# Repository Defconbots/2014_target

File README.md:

# Defconbots 2014 Target Hardware/Firmware

## Overview

This is the hardware and firmware design files for the defconbots 2014 laser target. It uses an [MSP430G2452](http://www.ti.com/product/msp430g2452) microcontroller and [TCS3414CS](http://www.ams.com/eng/Products/Light-Sensors/Color-Sensor/TCS3414) light detector to detect laser hits.

The board is designed in EagleCad 6.x. All part numbers are mouser numbers for easy BOM export.

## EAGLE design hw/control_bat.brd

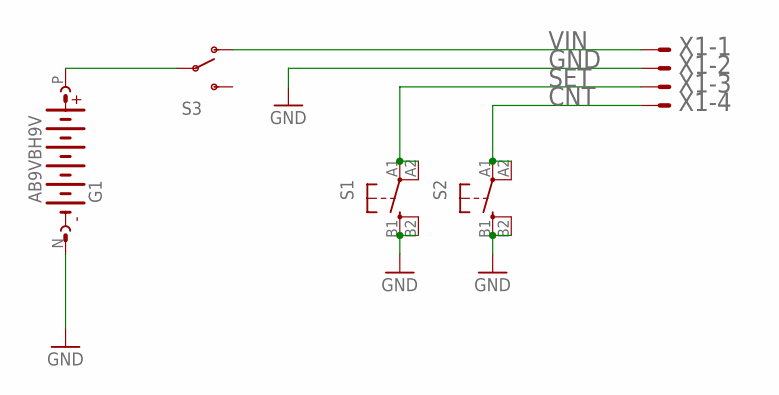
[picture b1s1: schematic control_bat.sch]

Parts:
G1: AB9VBH9V; BH9V-PC-ND
S1, S2: TAC_SWITCHD6F; D6F
S3: SWITCH-SPST; EG1270
X1: DF13-4P-1.25V(50); 53398-04

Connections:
CNT: S2.A1 (1), S2.A2 (2), X1.4
GND: G1.N (-), S1.B1 (3), S1.B2 (4), S2.B1 (3), S2.B2 (4), X1.2
unnamed: G1.P (+), S3.P$2
SET: S1.A1 (1), S1.A2 (2), X1.3
VIN: S3.P$1 (O), X1.1

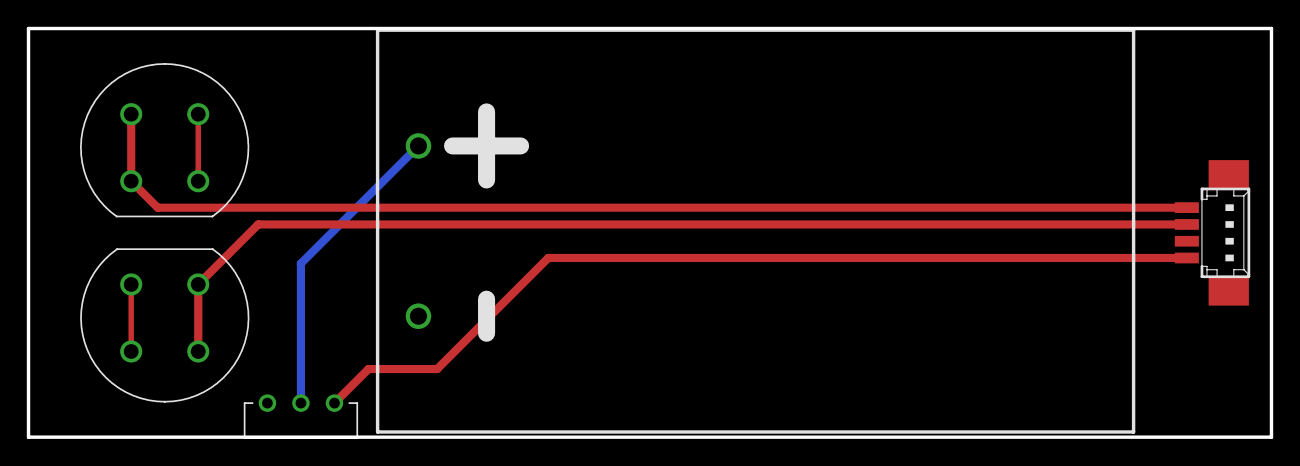
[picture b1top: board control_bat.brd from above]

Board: 2 copper layers, 92.7 x 30.5 mm, 5 parts (0 on the bottom side), 5 nets.

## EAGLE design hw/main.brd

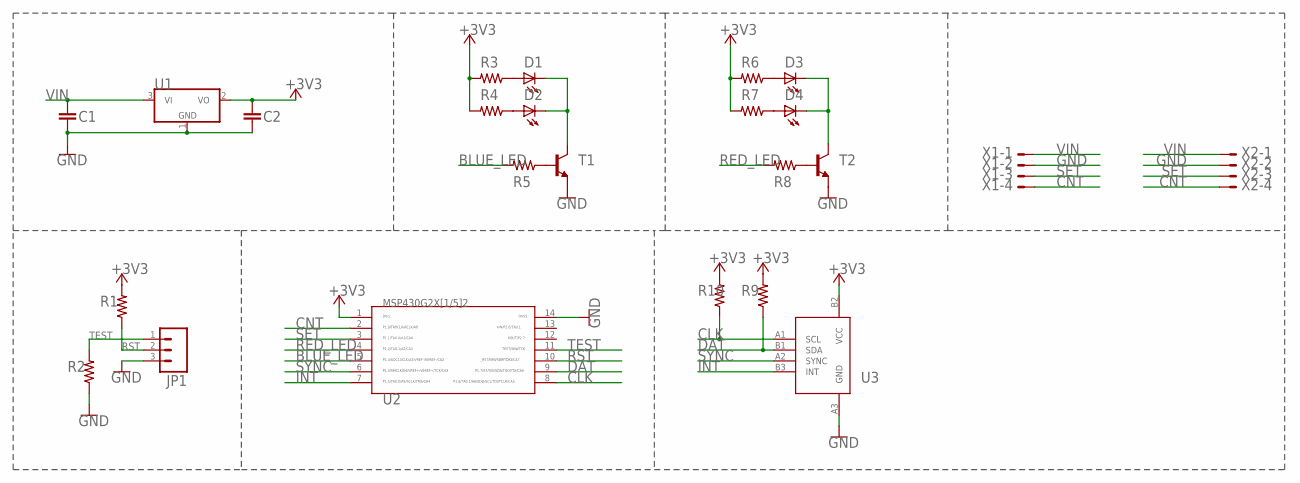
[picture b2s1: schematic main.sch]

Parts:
C1, C2: C1608X5R1C106M080AB; 0603-CAP
D1, D2: VLMB1300-GS08; LED-0603
D3, D4: VLMS1300-GS08; LED-0603
JP1: M03PTH; 1X03
R1, R2: RK73H1JTTD4702F; R0603
R3, R4, R5, R6, R7, R8: CRCW0603200RFKEA; R0603
R9, R10: RK73H1JTTD4701F; R0603
T1, T2: PMBT4401,215; SOT23-BEC
U1: MCP1703T-3002E/CB; SOT23
U2: MSP430G2452IPW14R; PW14
U3: TCS3414CS; CS-6
X1, X2: DF13-4P-1.25V(50); 53398-04

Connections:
+3V3: C2.1, R1.2, R3.2, R4.2, R6.2, R7.2, R9.2, R10.2, U1.2 (VO), U2.1, U3.B2 (VCC)
BLUE_LED: R5.2, U2.5
CLK: R10.1, U2.8, U3.A1 (SCL)
CNT: U2.2, X1.4, X2.4
DAT: R9.1, U2.9, U3.B1 (SDA)
GND: C1.2, C2.2, JP1.3, R2.1, T1.E, T2.E, U1.1 (GND), U2.14, U3.A3 (GND), X1.2, X2.2
INT: U2.7, U3.B3 (INT)
LED: D1.C, D2.C, T1.C
unnamed: D4.A, R7.1
unnamed: D3.C, D4.C, T2.C
unnamed: R8.1, T2.B
unnamed: D2.A, R4.1
unnamed: D1.A, R3.1
unnamed: D3.A, R6.1
unnamed: R5.1, T1.B
RED_LED: R8.2, U2.4
RST: JP1.2, R1.1, U2.10
SET: U2.3, X1.3, X2.3
SYNC: U2.6, U3.A2 (SYNC)
TEST: JP1.1, R2.2, U2.11
VIN: C1.1, U1.3 (VI), X1.1, X2.1

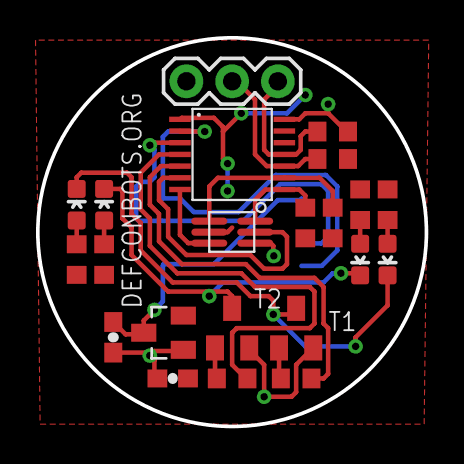
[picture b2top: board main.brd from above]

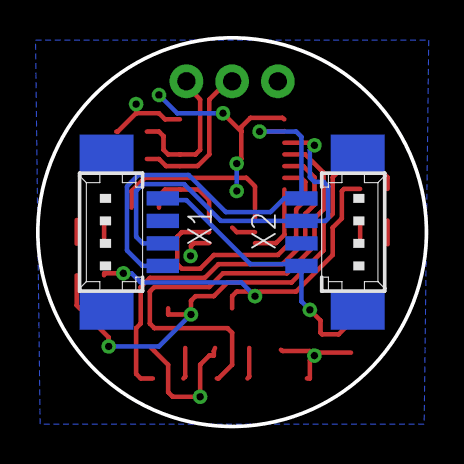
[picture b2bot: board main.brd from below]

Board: 2 copper layers, 21.6 x 21.6 mm, 24 parts (2 on the bottom side), 21 nets.

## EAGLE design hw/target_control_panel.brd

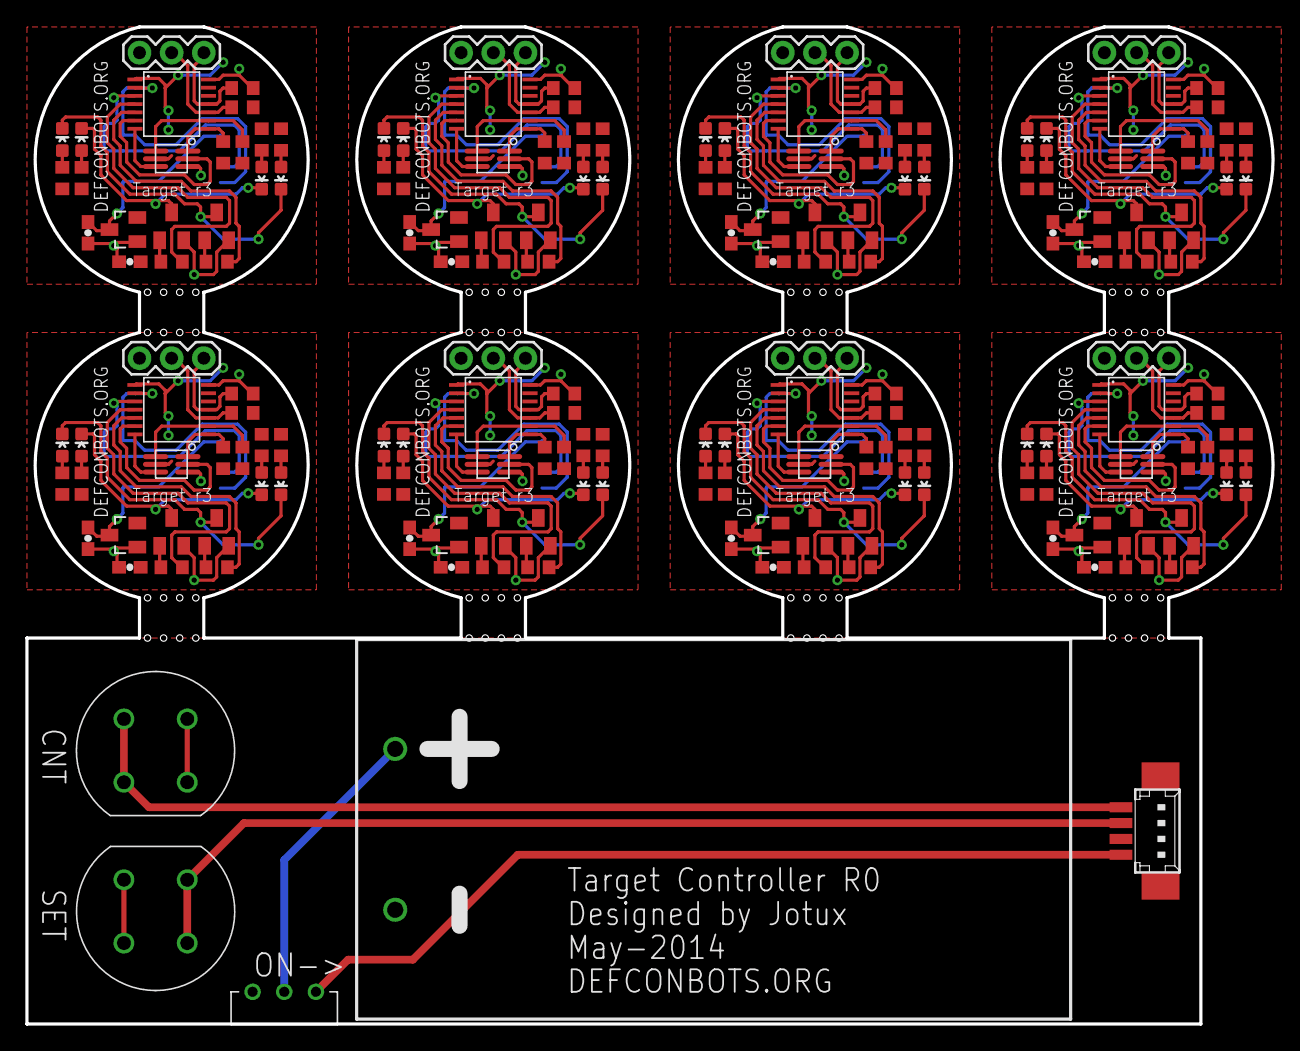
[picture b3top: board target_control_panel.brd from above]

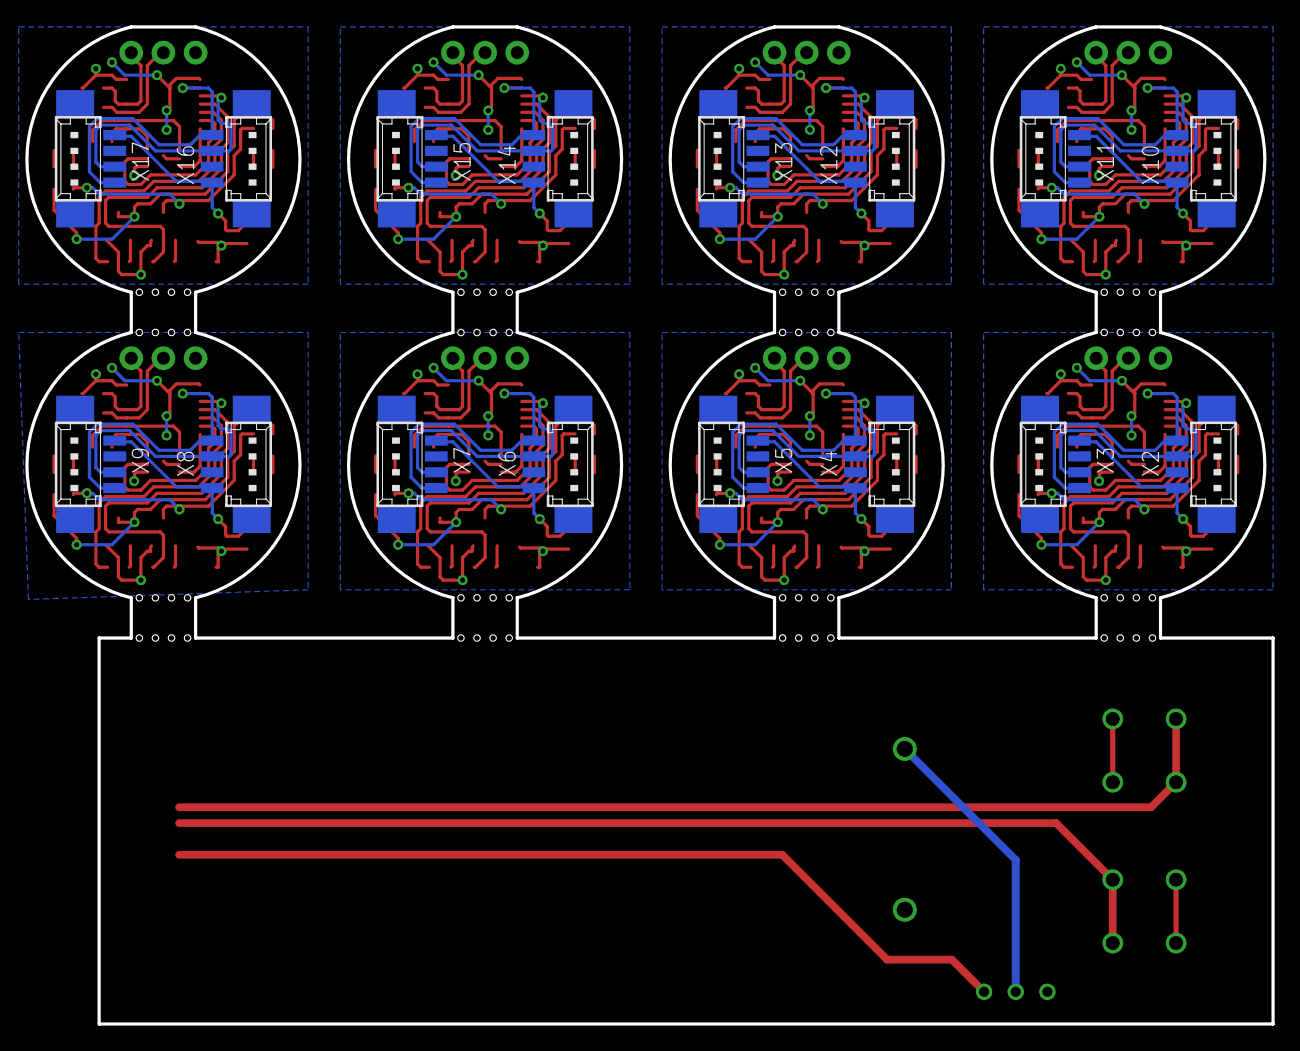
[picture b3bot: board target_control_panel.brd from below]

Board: 2 copper layers, 98.4 x 78.7 mm, 197 parts (16 on the bottom side), 173 nets.

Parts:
C1, C2, C3, C4, C5, C6, C7, C8, C9, C10, C11, C12, C13, C14, C15, C16: C1608X5R1C106M080AB; 0603-CAP
D1, D2, D5, D6, D9, D10, D13, D14, D17, D18, D21, D22, D25, D26, D29, D30: VLMB1300-GS08; LED-0603
D3, D4, D7, D8, D11, D12, D15, D16, D19, D20, D23, D24, D27, D28, D31, D32: VLMS1300-GS08; LED-0603
G1: AB9VBH9V; BH9V-PC-ND
JP1, JP2, JP3, JP4, JP5, JP6, JP7, JP8: 1X03
R1, R2, R15, R16, R25, R26, R35, R36, R45, R46, R55, R56, R65, R66, R75, R76: RK73H1JTTD4702F; R0603
R3, R4, R5, R6, R7, R8, R11, R12, R13, R14, R17, R18, R21, R22, R23, R24, R27, R28, R31, R32, R33, R34, R37, R38, R41, R42, R43, R44, R47, R48, R51, R52, R53, R54, R57, R58, R61, R62, R63, R64, R67, R68, R71, R72, R73, R74, R77, R78: CRCW0603200RFKEA; R0603
R9, R10, R19, R20, R29, R30, R39, R40, R49, R50, R59, R60, R69, R70, R79, R80: RK73H1JTTD4701F; R0603
S1, S2: D6F
S3: EG1270
T1, T2, T3, T4, T5, T6, T7, T8, T9, T10, T11, T12, T13, T14, T15, T16: PMBT4401,215; SOT23-BEC
U1, U4, U7, U10, U13, U16, U19, U22: MCP1703T-3002E/CB; SOT23
U2, U6, U9, U12, U15, U18, U21, U24: MSP430G2452IPW14R; PW14
U3, U5, U8, U11, U14, U17, U20, U23: TCS3414CS; CS-6
X1, X2, X3, X4, X5, X6, X7, X8, X9, X10, X11, X12, X13, X14, X15, X16, X17: DF13-4P-1.25V(50); 53398-04

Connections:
+3V1: C4.1, R11.2, R12.2, R14.2, R15.2, R17.2, R19.2, R20.2, U4.2, U5.B2, U6.1
+3V2: C6.1, R21.2, R22.2, R24.2, R25.2, R27.2, R29.2, R30.2, U7.2, U8.B2, U9.1
+3V3: C2.1, R1.2, R3.2, R4.2, R6.2, R7.2, R9.2, R10.2, U1.2, U2.1, U3.B2
+3V4: C8.1, R31.2, R32.2, R34.2, R35.2, R37.2, R39.2, R40.2, U10.2, U11.B2, U12.1
+3V5: C10.1, R41.2, R42.2, R44.2, R45.2, R47.2, R49.2, R50.2, U13.2, U14.B2, U15.1
+3V6: C12.1, R51.2, R52.2, R54.2, R55.2, R57.2, R59.2, R60.2, U16.2, U17.B2, U18.1
+3V7: C14.1, R61.2, R62.2, R64.2, R65.2, R67.2, R69.2, R70.2, U19.2, U20.B2, U21.1
+3V8: C16.1, R71.2, R72.2, R74.2, R75.2, R77.2, R79.2, R80.2, U22.2, U23.B2, U24.1
BLUE_LED: R5.2, U2.5
BLUE_LED1: R13.2, U6.5
BLUE_LED2: R23.2, U9.5
BLUE_LED3: R33.2, U12.5
BLUE_LED4: R43.2, U15.5
BLUE_LED5: R53.2, U18.5
BLUE_LED6: R63.2, U21.5
BLUE_LED7: R73.2, U24.5
CLK: R10.1, U2.8, U3.A1
CLK1: R20.1, U5.A1, U6.8
CLK2: R30.1, U8.A1, U9.8
CLK3: R40.1, U11.A1, U12.8
CLK4: R50.1, U14.A1, U15.8
CLK5: R60.1, U17.A1, U18.8
CLK6: R70.1, U20.A1, U21.8
CLK7: R80.1, U23.A1, U24.8
CNT: S2.A1, S2.A2, X1.4
CNT1: U2.2, X2.4, X3.4
CNT2: U6.2, X4.4, X5.4
CNT3: U9.2, X6.4, X7.4
CNT4: U12.2, X8.4, X9.4
CNT5: U15.2, X10.4, X11.4
CNT6: U18.2, X12.4, X13.4
CNT7: U21.2, X14.4, X15.4
CNT8: U24.2, X16.4, X17.4
DAT: R9.1, U2.9, U3.B1
DAT1: R19.1, U5.B1, U6.9
DAT2: R29.1, U8.B1, U9.9
DAT3: R39.1, U11.B1, U12.9
DAT4: R49.1, U14.B1, U15.9
DAT5: R59.1, U17.B1, U18.9
DAT6: R69.1, U20.B1, U21.9
DAT7: R79.1, U23.B1, U24.9
GND1: C1.2, C2.2, JP1.3, R2.1, T1.E, T2.E, U1.1, U2.14, U3.A3, X2.2, X3.2
GND2: C3.2, C4.2, JP2.3, R16.1, T3.E, T4.E, U4.1, U5.A3, U6.14, X4.2, X5.2
GND3: C5.2, C6.2, JP3.3, R26.1, T5.E, T6.E, U7.1, U8.A3, U9.14, X6.2, X7.2
GND4: C7.2, C8.2, JP4.3, R36.1, T7.E, T8.E, U10.1, U11.A3, U12.14, X8.2, X9.2
GND5: C9.2, C10.2, JP5.3, R46.1, T9.E, T10.E, U13.1, U14.A3, U15.14, X10.2, X11.2
GND6: C11.2, C12.2, JP6.3, R56.1, T11.E, T12.E, U16.1, U17.A3, U18.14, X12.2, X13.2
GND7: C13.2, C14.2, JP7.3, R66.1, T13.E, T14.E, U19.1, U20.A3, U21.14, X14.2, X15.2
GND8: C15.2, C16.2, JP8.3, R76.1, T15.E, T16.E, U22.1, U23.A3, U24.14, X16.2, X17.2
GND9: G1.N, S1.B1, S1.B2, S2.B1, S2.B2, X1.2
INT: U2.7, U3.B3
INT1: U5.B3, U6.7
INT2: U8.B3, U9.7
INT3: U11.B3, U12.7
INT4: U14.B3, U15.7
INT5: U17.B3, U18.7
INT6: U20.B3, U21.7
INT7: U23.B3, U24.7
LED: D1.C, D2.C, T1.C
LED1: D5.C, D6.C, T3.C
LED2: D9.C, D10.C, T5.C
LED3: D13.C, D14.C, T7.C
LED4: D17.C, D18.C, T9.C
LED5: D21.C, D22.C, T11.C
LED6: D25.C, D26.C, T13.C
LED7: D29.C, D30.C, T15.C
unnamed: D4.A, R7.1
unnamed: D3.C, D4.C, T2.C
unnamed: R8.1, T2.B
unnamed: G1.P, S3.P$2
unnamed: D5.A, R11.1
unnamed: D2.A, R4.1
unnamed: D1.A, R3.1
unnamed: D6.A, R12.1
unnamed: R13.1, T3.B
unnamed: D3.A, R6.1
unnamed: D7.A, R14.1
unnamed: D8.A, R17.1
unnamed: D7.C, D8.C, T4.C
unnamed: R18.1, T4.B
unnamed: D9.A, R21.1
unnamed: D10.A, R22.1
unnamed: R23.1, T5.B
unnamed: R5.1, T1.B
unnamed: D11.A, R24.1
unnamed: D12.A, R27.1
unnamed: D11.C, D12.C, T6.C
unnamed: R28.1, T6.B
unnamed: D13.A, R31.1
unnamed: D14.A, R32.1
unnamed: R33.1, T7.B
unnamed: D15.A, R34.1
unnamed: D16.A, R37.1
unnamed: D15.C, D16.C, T8.C
unnamed: R38.1, T8.B
unnamed: D17.A, R41.1
unnamed: D18.A, R42.1
unnamed: R43.1, T9.B
unnamed: D19.A, R44.1
unnamed: D20.A, R47.1
unnamed: D19.C, D20.C, T10.C
unnamed: R48.1, T10.B
unnamed: D21.A, R51.1
unnamed: D22.A, R52.1
unnamed: R53.1, T11.B
unnamed: D23.A, R54.1
unnamed: D24.A, R57.1
unnamed: D23.C, D24.C, T12.C
unnamed: R58.1, T12.B
unnamed: D25.A, R61.1
unnamed: D26.A, R62.1
unnamed: R63.1, T13.B
unnamed: D27.A, R64.1
unnamed: D28.A, R67.1
unnamed: D27.C, D28.C, T14.C
unnamed: R68.1, T14.B
unnamed: D29.A, R71.1
unnamed: D30.A, R72.1
unnamed: R73.1, T15.B
unnamed: D31.A, R74.1
unnamed: D32.A, R77.1
unnamed: D31.C, D32.C, T16.C
unnamed: R78.1, T16.B
RED_LED: R8.2, U2.4
RED_LED1: R18.2, U6.4
RED_LED2: R28.2, U9.4
RED_LED3: R38.2, U12.4
RED_LED4: R48.2, U15.4
RED_LED5: R58.2, U18.4
RED_LED6: R68.2, U21.4
RED_LED7: R78.2, U24.4
RST: JP1.2, R1.1, U2.10
RST1: JP2.2, R15.1, U6.10
RST2: JP3.2, R25.1, U9.10
RST3: JP4.2, R35.1, U12.10
RST4: JP5.2, R45.1, U15.10
RST5: JP6.2, R55.1, U18.10
RST6: JP7.2, R65.1, U21.10
RST7: JP8.2, R75.1, U24.10
SET: S1.A1, S1.A2, X1.3
SET1: U2.3, X2.3, X3.3
SET2: U6.3, X4.3, X5.3
SET3: U9.3, X6.3, X7.3
SET4: U12.3, X8.3, X9.3
SET5: U15.3, X10.3, X11.3
SET6: U18.3, X12.3, X13.3
SET7: U21.3, X14.3, X15.3
SET8: U24.3, X16.3, X17.3
SYNC: U2.6, U3.A2
SYNC1: U5.A2, U6.6
SYNC2: U8.A2, U9.6
SYNC3: U11.A2, U12.6
SYNC4: U14.A2, U15.6
SYNC5: U17.A2, U18.6
SYNC6: U20.A2, U21.6
SYNC7: U23.A2, U24.6
TEST: JP1.1, R2.2, U2.11
TEST1: JP2.1, R16.2, U6.11
TEST2: JP3.1, R26.2, U9.11
TEST3: JP4.1, R36.2, U12.11
TEST4: JP5.1, R46.2, U15.11
TEST5: JP6.1, R56.2, U18.11
TEST6: JP7.1, R66.2, U21.11
TEST7: JP8.1, R76.2, U24.11
VIN: S3.P$1, X1.1
VIN1: C1.1, U1.3, X2.1, X3.1
VIN2: C3.1, U4.3, X4.1, X5.1
VIN3: C5.1, U7.3, X6.1, X7.1
VIN4: C7.1, U10.3, X8.1, X9.1
VIN5: C9.1, U13.3, X10.1, X11.1
VIN6: C11.1, U16.3, X12.1, X13.1
VIN7: C13.1, U19.3, X14.1, X15.1
VIN8: C15.1, U22.3, X16.1, X17.1

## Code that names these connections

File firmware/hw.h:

/**
@file hw.h
@brief Definitions hardware config
@author Joe Brown
*/
#ifndef HW_H
#define HW_H
//::::::::::::::::::::::::::::::::::::::::::::::::::::::::::::::::::::::::::::::
//            __  __                  __
//           / / / /____ _ _____ ____/ /_      __ ____ _ _____ ___
//          / /_/ // __ `// ___// __  /| | /| / // __ `// ___// _ \
//         / __  // /_/ // /   / /_/ / | |/ |/ // /_/ // /   /  __/
//        /_/ /_/ \__,_//_/    \__,_/  |__/|__/ \__,_//_/    \___/
//
//::::::::::::::::::::::::::::::::::::::::::::::::::::::::::::::::::::::::::::::
// LEDs
#define RED             1,2
#define RED_ON()        HW_SET_HIGH(RED)
#define RED_OFF()       HW_SET_LOW(RED)
#define RED_TOGGLE()    HW_SET_TOGGLE(RED)

#define BLUE            1,3
#define BLUE_ON()       HW_SET_HIGH(BLUE)
#define BLUE_OFF()      HW_SET_LOW(BLUE)
#define BLUE_TOGGLE()   HW_SET_TOGGLE(BLUE)

// Inter-module comm.
#define CNT             1,0
#define CNT_READ()      HW_READ(CNT)
#define SET             1,1
#define SET_READ()      HW_READ(SET)

// Interrupt config
#define NUM_P1_INTS     4

// Light sensor
#define SYNC            1,4
#define SYNC_LOW()      HW_SET_LOW(SYNC)
#define INT             1,5

#define DAT             1,7
#define DAT_LOW()       HW_SET_LOW(DAT)
#define DAT_HIGH()      HW_SET_HIGH(DAT)
#define DAT_INPUT()     HW_INPUT(DAT)
#define DAT_OUTPUT()    HW_OUTPUT(DAT)
#define DAT_READ()      HW_READ(DAT)
#define CLK             1,6
#define CLK_LOW()       HW_SET_LOW(CLK)
#define CLK_HIGH()      HW_SET_HIGH(CLK)
#define CLK_INPUT()     HW_INPUT(CLK)
#define CLK_OUTPUT()    HW_OUTPUT(CLK)

#endif

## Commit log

2013-10-17 Update readme with part number and tool info.
2013-10-27 Rename repo to generic target and add firmware. Firmware is notional right now and is unlikely to even compile.
2013-10-27 Fix pin on laser input
2013-10-29 It compiles, and that's it
2013-10-29 Hw up and running with dasblinkenlights sample
2013-11-02 Detects laster hits and blinks the green LED for each hit detected.
2013-11-13 Minor bug where PublishEvent never returned a fail.
2013-11-13 Remove transistor and switch laser input to ADC polling.
2013-11-14 Fix resistor value for light detector.
2014-01-09 Fix tabs...
2014-04-03 Updated target to simplify circuit and make immune to spurious light sources.
    The design has been reduced in size from ~40mm diameter to ~21mm diameter. The sensor was changed from a single-color (red) detector to a full-spectrum + white sensor since the old version would get 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
2014-04-18 Fix errors in PCB found after initial testing.
    - Swapped pullup/down on RST/TEST lines (they were backward).
    - Added 4.7k pullups to i2c lines (maybe don't need but the signal is a little ugly without them)
    - Removed silkscreen of part numbers since they're not very readable anyway
2014-04-18 Preliminary firmware for rev2 hardware.
    - Updated hw defs for new board
    - Added bitbanged i2c driver (USI on the g2452 was cumbersome)
    - Added tcs3414 light sensor driver
    - Initial code just reads clear channel for demo
    - Other minor tweaks
2014-04-19 Add 3d models for train and PCB mount hardware
2014-04-25 Fix HW_PULL_UP/DOWN macro.
2014-04-25 First pass implementing logic for target with new sensor. Also implemented intermodule config/halt.
2014-04-28 Fix bug where events could get pushed in the middle of state transitions and not get detected.
2014-04-28 Refine target implementation.
    -Add ambient-light detection on powerup
    -Clean up delay functions (pass number of milliseconds instead of num * millisecond)
    -Tune color sensor
    -Add blink to show kill count setting
2014-04-28 Clean up red LED behavior.
2014-04-30 Add battery/control board.
2014-05-01 Fix battery orientation in control board. Panelize for manufacturing.
2014-05-03 Remove adc, since we don't need it.
2014-05-03 Add some juiciness to the LEDs. Tweak detection settings. Add hit and reset broadcasting.
2014-05-15 Extend BroadcastReset Delays to ensure they are detected on the other targets and add ifdef to disable pullups.
    If pullups are enabled on all the targets then when a target detects a hit it will not be able to pull the line low. We could add pullups on the control board but since there is no regulation there i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
2014-05-28 Switch cnt/set to polling. Minor tweaks for usability.
2014-06-02 Tweaks for hit broadcast, hit detection, and spurious light immunity.
2014-06-03 Fix bug where blue LED would turn off, beautifully, when a hit was broadcast to a dead unit
2014-11-09 Axe the info section I'm never going to update.

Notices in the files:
parts and their libraries:
SparkFun-LED: Licensing: CC v3.0 Share-Alike You are welcome to use this library for commercial purposes.
SparkFun-Connectors: Licensing: Creative Commons ShareAlike 4.0 International - https://creativecommons.org/licenses/by-sa/4.0
